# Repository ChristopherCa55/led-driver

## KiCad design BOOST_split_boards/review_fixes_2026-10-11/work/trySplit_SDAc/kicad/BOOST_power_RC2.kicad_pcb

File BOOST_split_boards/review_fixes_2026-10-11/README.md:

# Review fixes, 2026-10-11 (work folder)

Fixes for the 2026-10-10 schematic and PCB reviews, run from `review_2026-10-10/FIX_PROMPT.md`.

- **The copy:** `led-driver/BOOST_review_fixes/` = BOOST_package as of 2026-10-11 (12 key files hash-checked against
  all three shipped folders; lock files, `.history` and `.kicad_prl` left out), plus `NOT_FOR_FAB.txt`.
- **The shipped folders are never written.**
- **Status (2026-10-13):** every approved step is in the copy (steps 1-4, 5g, 6b, 7e, 8c, 9, 10) and every output
  was regenerated; the copy stays NOT_FOR_FAB until the user says ship. Read the top of `FIX_REPORT.md`, then
  `CHANGES_XY.md`.
- **Answers:** `ANSWERS.md` (the user's words and how each was applied).

## Layout
- `DECISIONS.md`: the decisions asked in one batch, with numbers, options and recommendations.
- `work/baseline/`: every check on the unmodified copy (run on a scratch copy of its KiCad folder, so no `.kicad_prl`
  lands in the copy).
- `work/METRICS.md`: one row per metric, one column per step; `work/METRICS_final.md`: baseline / the copy now / with
  the pending steps. `work/CHANGELOG.md`: every step, failed tries included. `work/promotions.log`: every file written
  into the copy, old -> new hash.
- `work/stepNN/`: each step's scratch KiCad folder, its spec, gates (`step_checks.log`), metrics outputs and `STEP.md`.
  Failed tries keep their folder with a `FAILED.txt` or `SUPERSEDED.txt`.
- `work/specs/`: the edit specs (pcb_text_edit / route_new / add_footprints jobs).
- `work/final_copy_check/`: the final gates run on the copy's own files.
- `work/pristine/`: untouched copies of the copy's KiCad and LTspice folders, the references for checks.
- `work/proto/*_NOT_FOR_FAB/`: research prototypes on scratch boards. These are not steps of the fix.
- `work/whatif/`: what-if solves on edited copies of the copper export.
- `work/sims/`: LTspice runs (`.save` list; the shipped `.tran`).
- `work/mockups/`, `img/mock/`: note and title mock-ups (scratch schematics only).
- `img/research/`: net maps used for planning.

## Tools (`tools/`)
| Tool | What it does |
|---|---|
| `make_copy.py` | Makes the copy, leaving out lock files and KiCad backups; checks every copied file's hash. |
| `step_checks.sh STEP` | Runs every gate and metric on `STEP/kicad`: ERC x3, DRC with refill and parity, sync, both exports, DC solve, loop L, pcb_checks, plane / sense cover, gate returns, GND heatmap with sense offsets, card sens_check6, and the U16 thermal model (`THERMAL=1`). |
| `collect.py WORK STEP...` | Builds METRICS.md and flags anything worse than the baseline. |
| `sense_cover.py` | Sense nets over GND. Rebuilt; reproduces the 10-02 per-net figures exactly. |
| `sense_offsets.py` | LED-sense GND offsets to the card's GND. Rebuilt; reproduces 10-02 exactly. |
| `gates_all.sh` | gate_return.py for all ten gate paths. |
| `sim_case.py` | One LTspice run on a scratch copy, editing the netlist only (`.save` list, extra `.meas`, `.ic` variants). |
| `d19_cycles.py` | D19 conduction per switching cycle from a run. |
| `pcb_text_edit.py SPEC IN OUT` | Removes / adds segments and vias by text edit (CRLF kept); OUT must not exist. |
| `whatif_vias.py` | Adds vias to a copper export, with antipads and a collision check. |
| `net_map.py` | Plan view of a net on all layers. |
| `mock_notes.py`, `mock_kicad.py` | Note and title mock-ups into new scratch files. |

## Lessons
- **Run heavy jobs one at a time.** Two 9-worker DC solves at once crash (BrokenProcessPool, out of memory). Running
  solves alongside LTspice grew the page file to 46 GB.
- **Headless Edge from Python** writes no screenshot when its output is piped. Log it to a file and wait for the PNG.
- **DC solves run out of memory with 5-9 workers** while the user's apps hold ~20 GB; 3 workers work (~30 min).
- **A via with no track or pad needs `(free yes)`**, or KiCad gives it a zone's net (step 7's first try became 5V).
- **The card's GND is in the Power netclass (0.25 mm clearance)**, not Default (0.2 mm).
- **Never edit a bash script while it runs** (bash reads it as it goes; step 3's make_step.sh broke that way).
- **Git Bash's `grep -c $'\r'` counts every line**: count CRLF in Python.
- **The 6-layer card is saturated:** the longest In1 splitters (0err_hi, SDA) have no route on In2 / F / B.

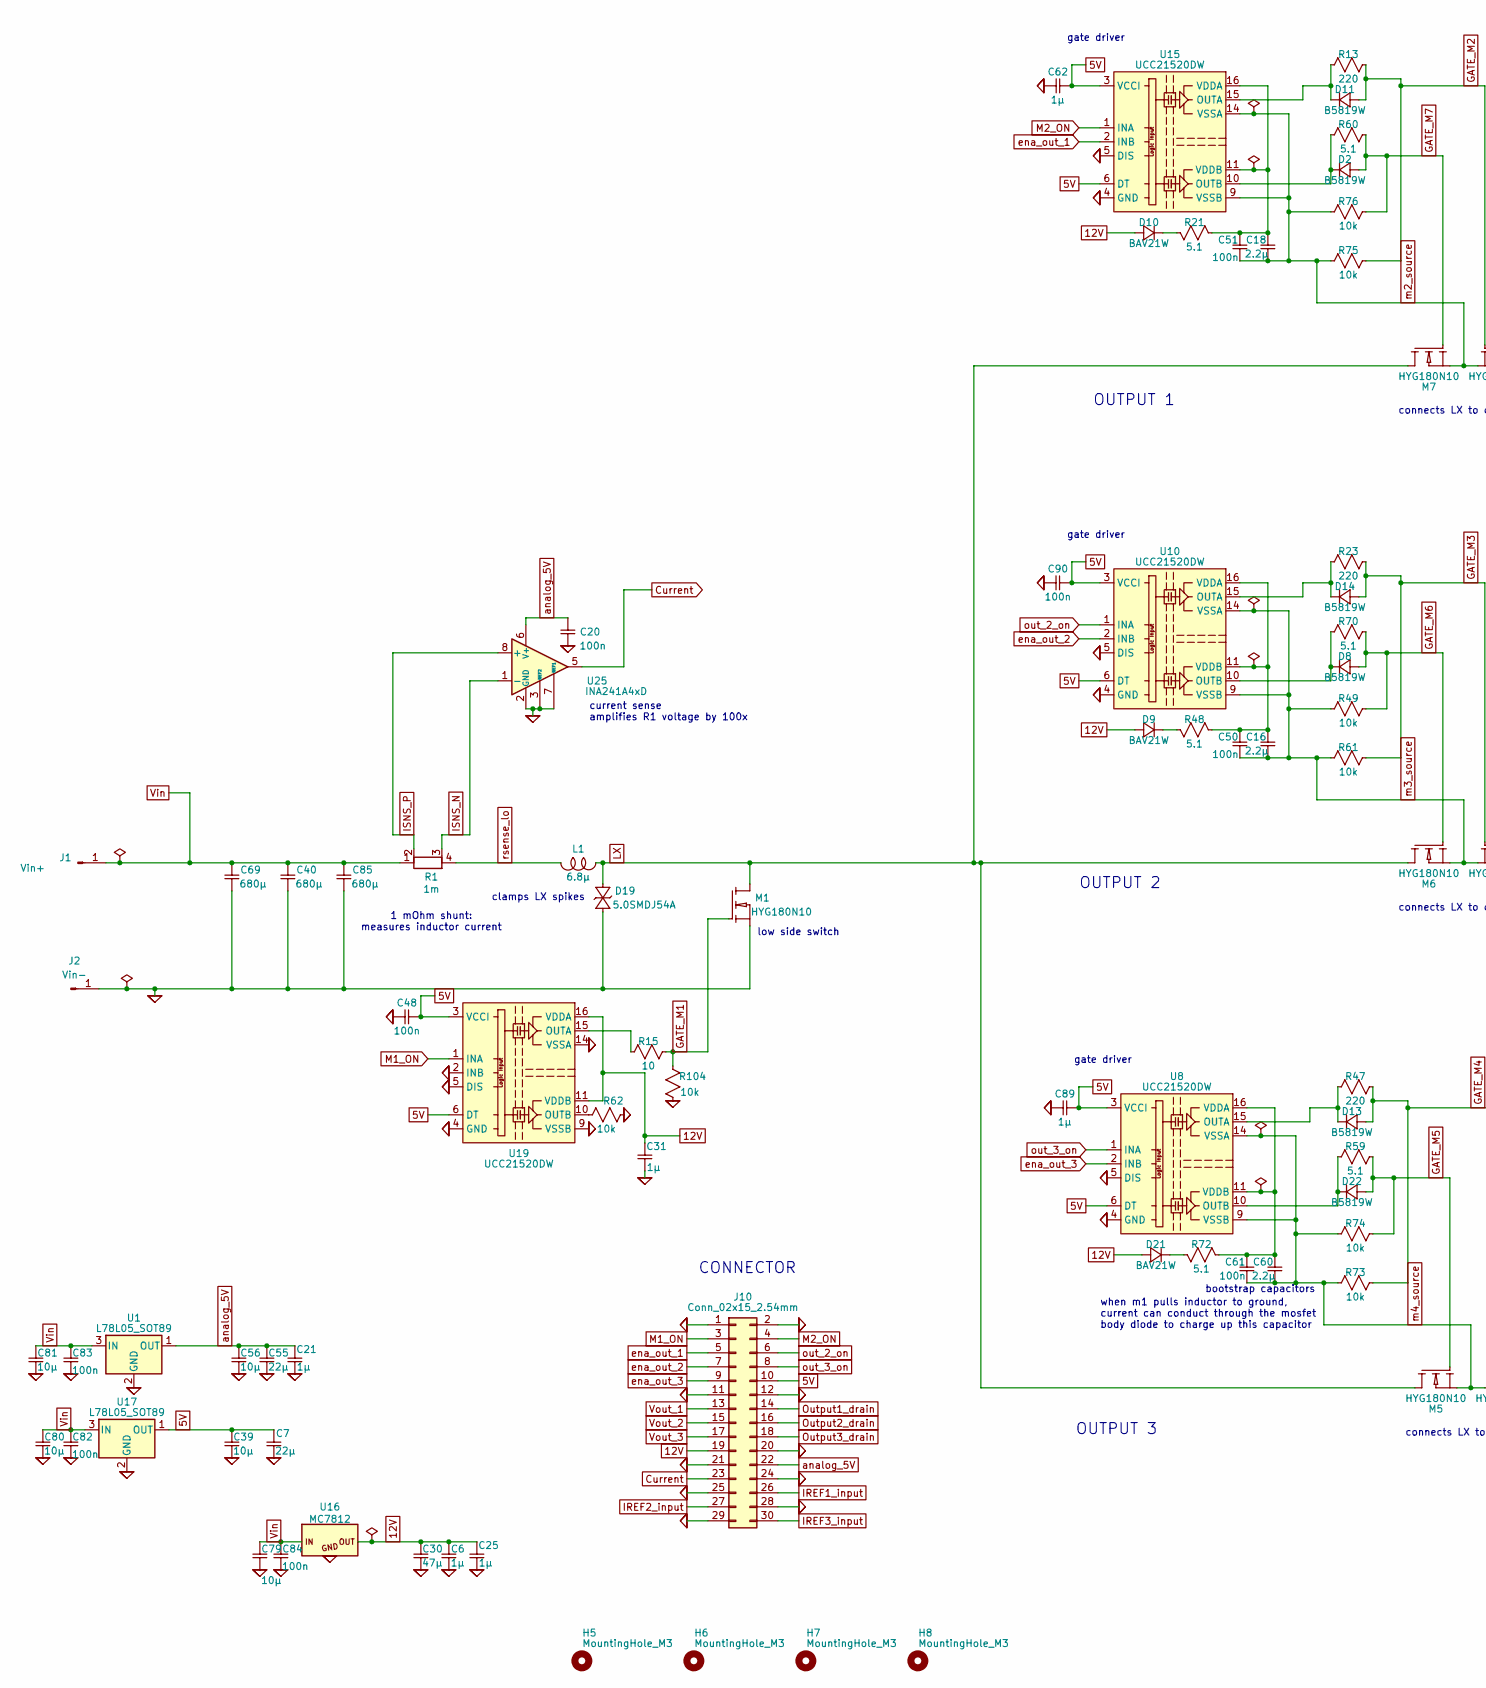
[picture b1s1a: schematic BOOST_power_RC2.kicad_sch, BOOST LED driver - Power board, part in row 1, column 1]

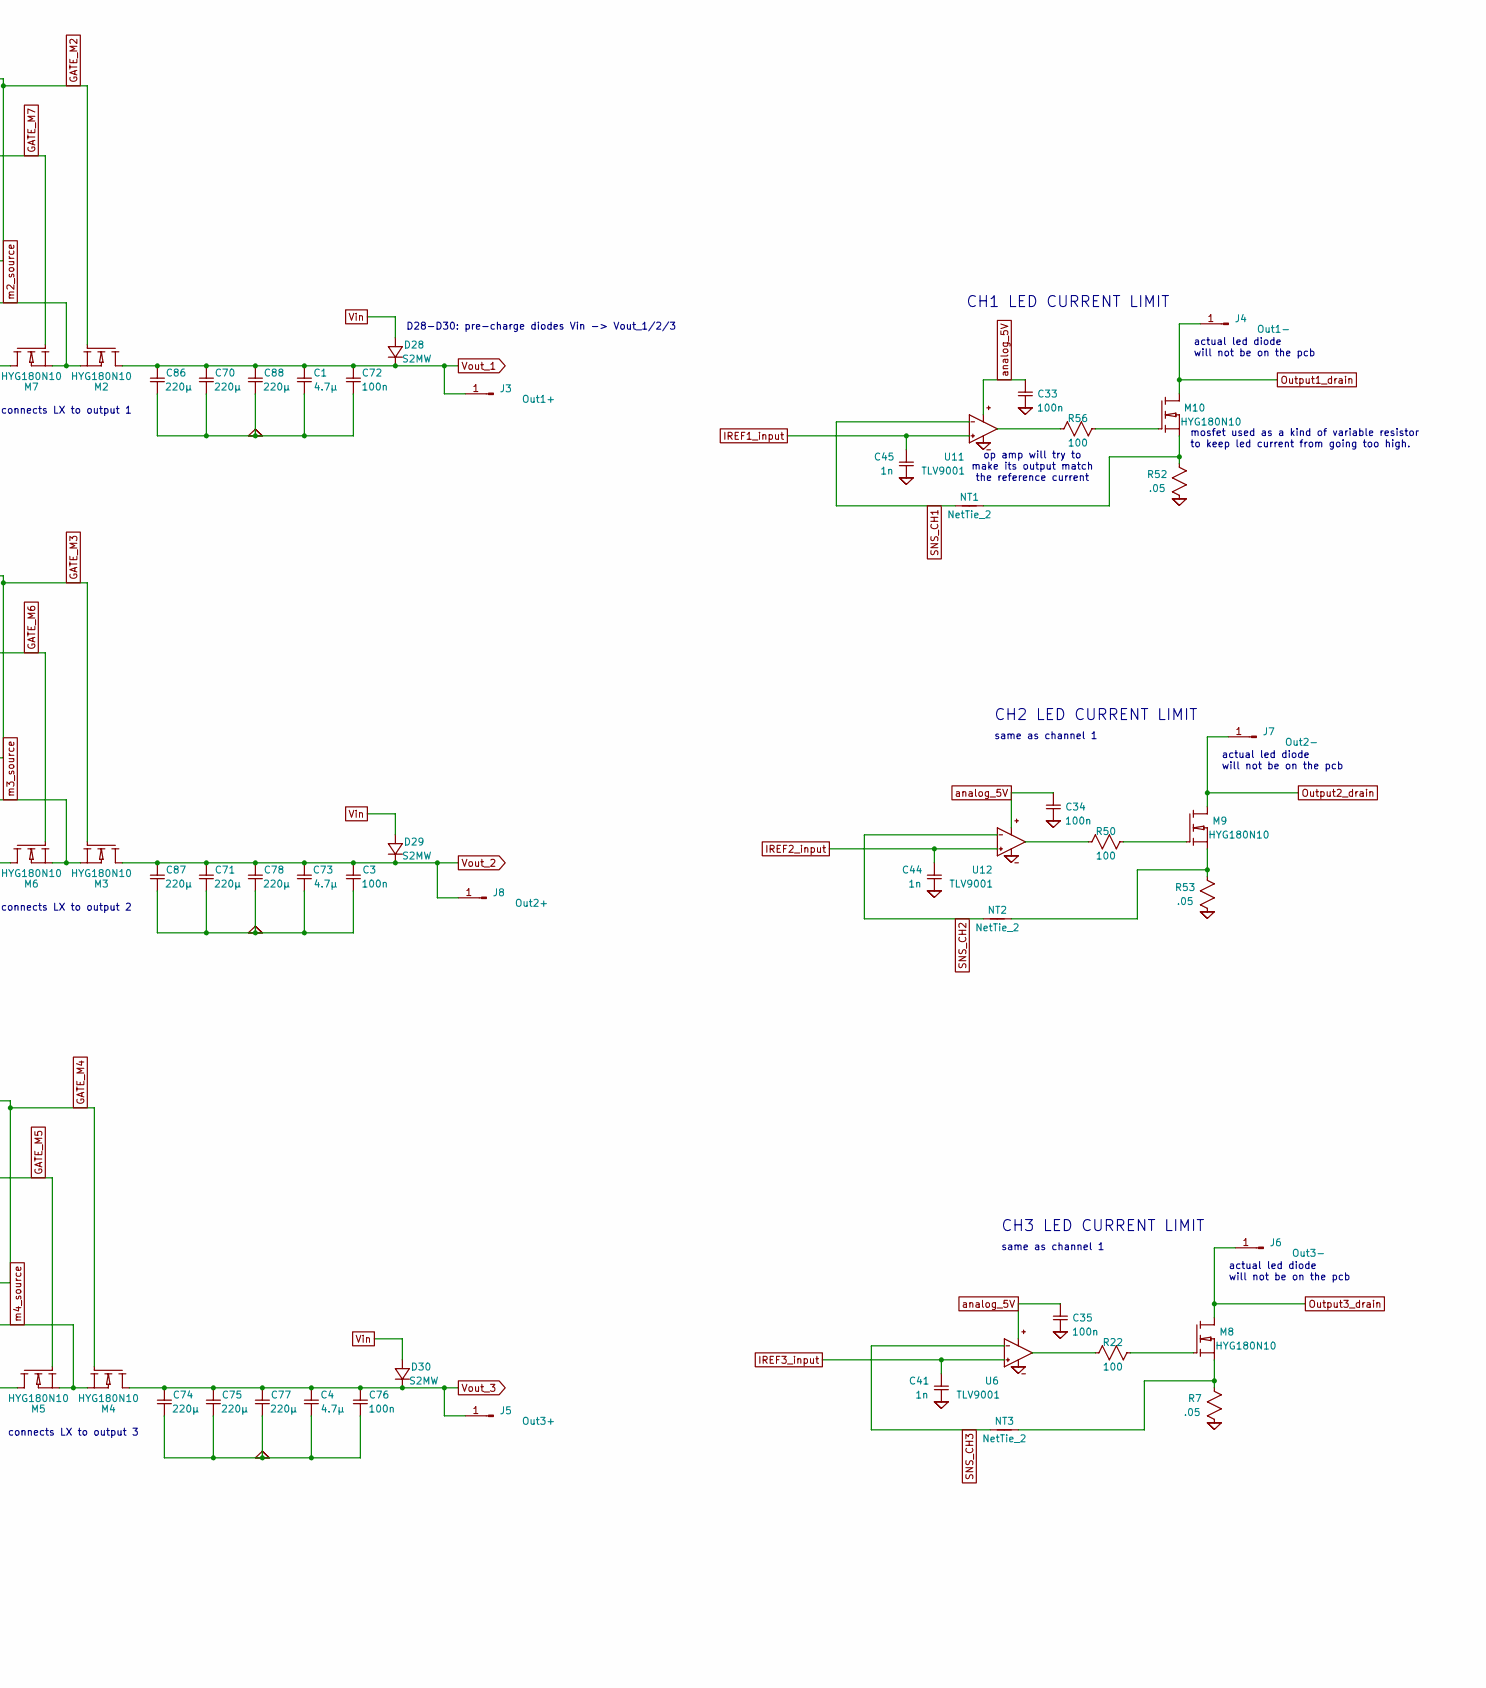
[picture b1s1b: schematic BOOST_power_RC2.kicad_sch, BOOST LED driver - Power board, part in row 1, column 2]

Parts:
C1, C4, C73: 4.7µ; C_1210_3225Metric
C3, C72, C76: 100n; C_0805_2012Metric
C6, C21, C25, C31, C62, C89: 1µ; C_0805_2012Metric
C7, C55: 22µ; C_1210_3225Metric; MPN GRM32ER71E226KE15L; LCSC C21397
C16, C18, C60: 2.2µ; C_1206_3216Metric
C20, C33, C34, C35, C48, C50, C51, C61, C82, C83, C84, C90: 100n; C_0603_1608Metric
C30: 47µ; CP_EIA-7343-31_Kemet-D; MPN TR3D476K025C0250; LCSC C4979367
C39, C56, C79, C80, C81: 10µ; C_1210_3225Metric
C40, C69, C85: 680µ; CP_Elec_10x12.5; MPN EEH-ZU1E681UP; LCSC C29664285
C41, C44, C45: 1n; C_0603_1608Metric
C70, C71, C75, C77, C78, C88: 220µ; CP_Elec_10x16.5; MPN EEH-ZS1H221P
C74, C86, C87: 220µ; CP_Elec_10x16.5; MPN EEH-ZU1H221P
D2, D8, D11, D13, D14, D22: B5819W; D_SOD-123
D9, D10, D21: BAV21W; D_SOD-123
D19: 5.0SMDJ54A; D_SMC; MPN 5.0SMDJ54A; LCSC C20415356
D28, D29, D30: S2MW; D_SOD-123F; MPN S2MW; LCSC C128729
H5, H6, H7, H8: MountingHole_M3; MountingHole_3.2mm_M3
J1: Vin+; MountingHole_4.3mm_M4_Pad7.0_TopBottom
J2: Vin-; MountingHole_4.3mm_M4_Pad7.0_TopBottom
J3: Out1+; TestPoint_THTPad_4.0x4.0mm_Drill2.0mm
J4: Out1-; TestPoint_THTPad_4.0x4.0mm_Drill2.0mm
J5: Out3+; TestPoint_THTPad_4.0x4.0mm_Drill2.0mm
J6: Out3-; TestPoint_THTPad_4.0x4.0mm_Drill2.0mm
J7: Out2-; TestPoint_THTPad_4.0x4.0mm_Drill2.0mm
J8: Out2+; TestPoint_THTPad_4.0x4.0mm_Drill2.0mm
J10: Conn_02x15_2.54mm; PinSocket_2x15_P2.54mm_Vertical; MPN ESQ-115-44-G-D
L1: 6.8µ; IND_CSCF3218-6R8MC
M1, M8, M9, M10: HYG180N10; TO-220-3_Horizontal_TabUp_M2.5
M2, M3, M4, M5, M6, M7: HYG180N10; TO-220-3_Horizontal_TabUp_NoHole
NT1, NT2, NT3: NetTie_2; NetTie-2_SMD_Pad0.5mm
R1: 1m; R_Bourns_CSS4J-4026; MPN CSS4J-4026R-1L00F; LCSC C2076400
R7, R52, R53: .05; R_2512_6332Metric
R13, R23, R47: 220; R_0603_1608Metric
R15: 10; R_0805_2012Metric
R21, R48, R60, R72: 5.1; R_0805_2012Metric; MPN 0805W8F510KT5E; LCSC C17724
R22, R50, R56: 100; R_0603_1608Metric
R49, R61, R62, R73, R74, R75, R76, R104: 10k; R_0603_1608Metric
R59, R70: 5.1; R_0805_2012Metric
U1, U17: L78L05_SOT89; SOT-89-3
U6, U11, U12: TLV9001; SOT-23-5; MPN TLV9001IDBVR
U8, U10, U15, U19: UCC21520DW; SOIC-16W_7.5x10.3mm_P1.27mm
U16: MC7812; TO-263-3_TabPin2; MPN MC7812BD2TR4G
U25: INA241A4xD; SOIC-8_3.9x4.9mm_P1.27mm; MPN INA241A4IDR; LCSC C22427873

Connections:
5V: C7.1, C39.1, C48.1, C62.2, C89.2, C90.1, J10.10, U8.3 (VCCI), U8.6 (DT), U8.8 (VCCI), U10.3 (VCCI), U10.6 (DT), U10.8 (VCCI), U15.3 (VCCI), U15.6 (DT), U15.8 (VCCI), U17.1 (OUT), U19.3 (VCCI), U19.6 (DT), U19.8 (VCCI)
12V: C6.1, C25.1, C30.1, C31.1, D9.2 (+), D10.2 (+), D21.2 (+), J10.19, U16.3 (OUT), U19.11 (VDDB), U19.16 (VDDA)
Current: J10.23, U25.5
GATE_M1: M1.1 (G), R15.2, R104.1
GATE_M2: D11.2 (+), M2.1 (G), R13.1, R75.2
GATE_M3: D14.2 (+), M3.1 (G), R23.2, R61.2
GATE_M4: D13.2 (+), M4.1 (G), R47.1, R73.2
GATE_M5: D22.2 (+), M5.1 (G), R59.1, R74.2
GATE_M6: D8.2 (+), M6.1 (G), R49.1, R70.2
GATE_M7: D2.2 (+), M7.1 (G), R60.2, R76.2
GND: C1.2, C3.2, C4.2, C6.2, C7.2, C20.2, C21.2, C25.2, C30.2, C31.2, C33.2, C34.2, C35.2, C39.2, C40.2, C41.2, C44.2, C45.2, C48.2, C55.2, C56.2, C62.1, C69.2, C70.2, C71.2, C72.2, C73.2, C74.2, C75.2, C76.2, C77.2, C78.2, C79.2, C80.2, C81.2, C82.2, C83.2, C84.2, C85.2, C86.2, C87.2, C88.2, C89.1, C90.2, D19.2 (+), J2.1, J10.1, J10.2, J10.11, J10.12, J10.20, J10.21, J10.24, J10.25, J10.28, J10.29, M1.3 (S), R7.2, R52.2, R53.2, R62.2, R104.2, U1.2 (GND), U6.2 (V-), U8.4 (GND), U8.5 (DIS), U10.4 (GND), U10.5 (DIS), U11.2 (V-), U12.2 (V-), U15.4 (GND), U15.5 (DIS), U16.2 (GND), U17.2 (GND), U19.2 (INB), U19.4 (GND), U19.5 (DIS), U19.9 (VSSB), U19.14 (VSSA), U25.2 (GND), U25.3 (REF2), U25.4 (GND), U25.7 (REF1)
IREF1_input: C45.1, J10.26, U11.3 (In+)
IREF2_input: C44.1, J10.27, U12.3 (In+)
IREF3_input: C41.1, J10.30, U6.3 (In+)
ISNS_N: R1.3, U25.1 (-)
ISNS_P: R1.2, U25.8 (+)
LX: D19.1 (-), L1.1, M1.2 (D), M5.2 (D), M6.2 (D), M7.2 (D)
M1_ON: J10.3, U19.1 (INA)
M2_ON: J10.4, U15.1 (INA)
unnamed: D2.1 (-), R60.1, U15.10 (OUTB)
unnamed: D8.1 (-), R70.1, U10.10 (OUTB)
unnamed: D9.1 (-), R48.1
unnamed: D10.1 (-), R21.1
unnamed: D11.1 (-), R13.2, U15.15 (OUTA)
unnamed: D13.1 (-), R47.2, U8.15 (OUTA)
unnamed: D14.1 (-), R23.1, U10.15 (OUTA)
unnamed: D21.1 (-), R72.1
unnamed: D22.1 (-), R59.2, U8.10 (OUTB)
unnamed: M8.1 (G), R22.1
unnamed: M8.3 (S), NT3.2, R7.1
unnamed: M9.1 (G), R50.1
unnamed: M9.3 (S), NT2.2, R53.1
unnamed: M10.1 (G), R56.1
unnamed: M10.3 (S), NT1.2, R52.1
unnamed: R22.2, U6.1 (OUT)
unnamed: C60.1, C61.1, R72.2, U8.11 (VDDB), U8.16 (VDDA)
unnamed: C16.1, C50.1, R48.2, U10.11 (VDDB), U10.16 (VDDA)
unnamed: R56.2, U11.1 (OUT)
unnamed: R50.2, U12.1 (OUT)
unnamed: C18.1, C51.1, R21.2, U15.11 (VDDB), U15.16 (VDDA)
unnamed: R15.1, U19.15 (OUTA)
unnamed: R62.1, U19.10 (OUTB)
Output1_drain: J4.1 (Pin_1_1), J10.14, M10.2 (D)
Output2_drain: J7.1 (Pin_1_1), J10.16, M9.2 (D)
Output3_drain: J6.1 (Pin_1_1), J10.18, M8.2 (D)
SNS_CH1: NT1.1, U11.4 (In-)
SNS_CH2: NT2.1, U12.4 (In-)
SNS_CH3: NT3.1, U6.4 (In-)
Vin: C40.1, C69.1, C79.1, C80.1, C81.1, C82.1, C83.1, C84.1, C85.1, D28.2 (+), D29.2 (+), D30.2 (+), J1.1, R1.1, U1.3 (IN), U16.1 (IN), U17.3 (IN)
Vout_1: C1.1, C70.1, C72.1, C86.1, C88.1, D28.1 (-), J3.1 (Pin_1_1), J10.13, M2.2 (D)
Vout_2: C3.1, C71.1, C73.1, C78.1, C87.1, D29.1 (-), J8.1 (Pin_1_1), J10.15, M3.2 (D)
Vout_3: C4.1, C74.1, C75.1, C76.1, C77.1, D30.1 (-), J5.1 (Pin_1_1), J10.17, M4.2 (D)
analog_5V: C20.1, C21.1, C33.1, C34.1, C35.1, C55.1, C56.1, J10.22, U1.1 (OUT), U6.5 (V+), U11.5 (V+), U12.5 (V+), U25.6 (V+)
ena_out_1: J10.5, U15.2 (INB)
ena_out_2: J10.7, U10.2 (INB)
ena_out_3: J10.9, U8.2 (INB)
m2_source: C18.2, C51.2, M2.3 (S), M7.3 (S), R75.1, R76.1, U15.9 (VSSB), U15.14 (VSSA)
m3_source: C16.2, C50.2, M3.3 (S), M6.3 (S), R49.2, R61.1, U10.9 (VSSB), U10.14 (VSSA)
m4_source: C60.2, C61.2, M4.3 (S), M5.3 (S), R73.1, R74.1, U8.9 (VSSB), U8.14 (VSSA)
out_2_on: J10.6, U10.1 (INA)
out_3_on: J10.8, U8.1 (INA)
rsense_lo: L1.2, R1.4

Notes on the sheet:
CH1 LED CURRENT LIMIT
OUTPUT 1
OUTPUT 2
current sense amplifies R1 voltage by 100x
gate driver
CH2 LED CURRENT LIMIT
when m1 pulls inductor to ground, current can conduct through the mosfet body diode to charge up this capacitor
OUTPUT 3
same as channel 1
op amp will try to make its output match the reference current
low side switch
mosfet used as a kind of variable resistor to keep led current from going too high.
1 mOhm shunt: measures inductor current
bootstrap capacitors
connects LX to output 3
clamps LX spikes
CH3 LED CURRENT LIMIT
CONNECTOR
D28-D30: pre-charge diodes Vin -> Vout_1/2/3
connects LX to output 2
actual led diode will not be on the pcb
connects LX to output 1

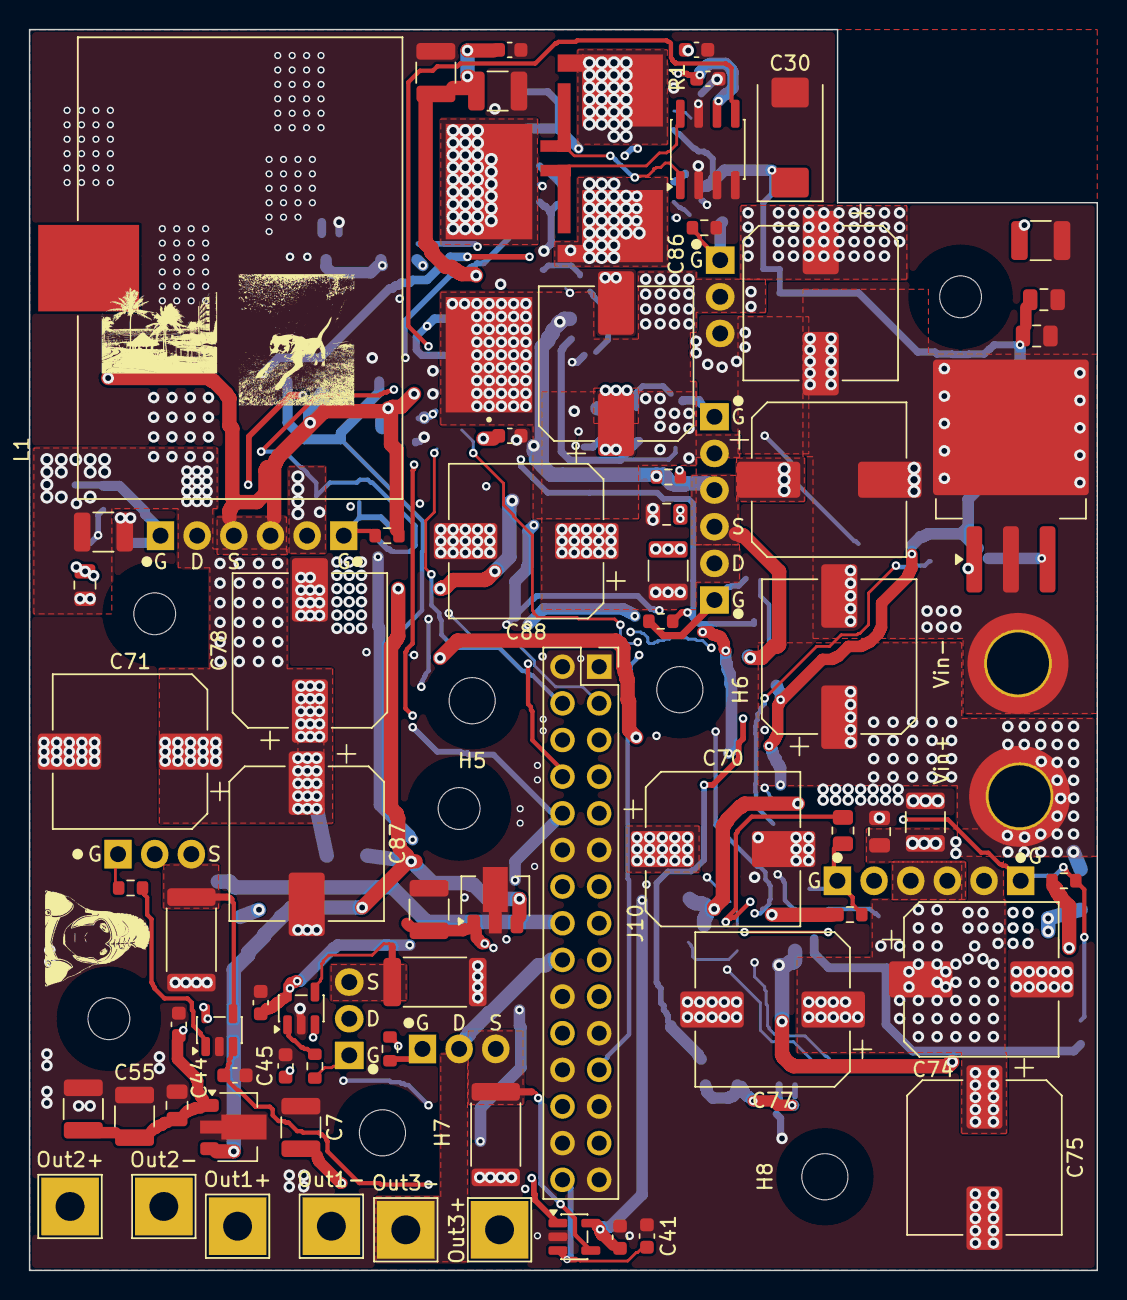
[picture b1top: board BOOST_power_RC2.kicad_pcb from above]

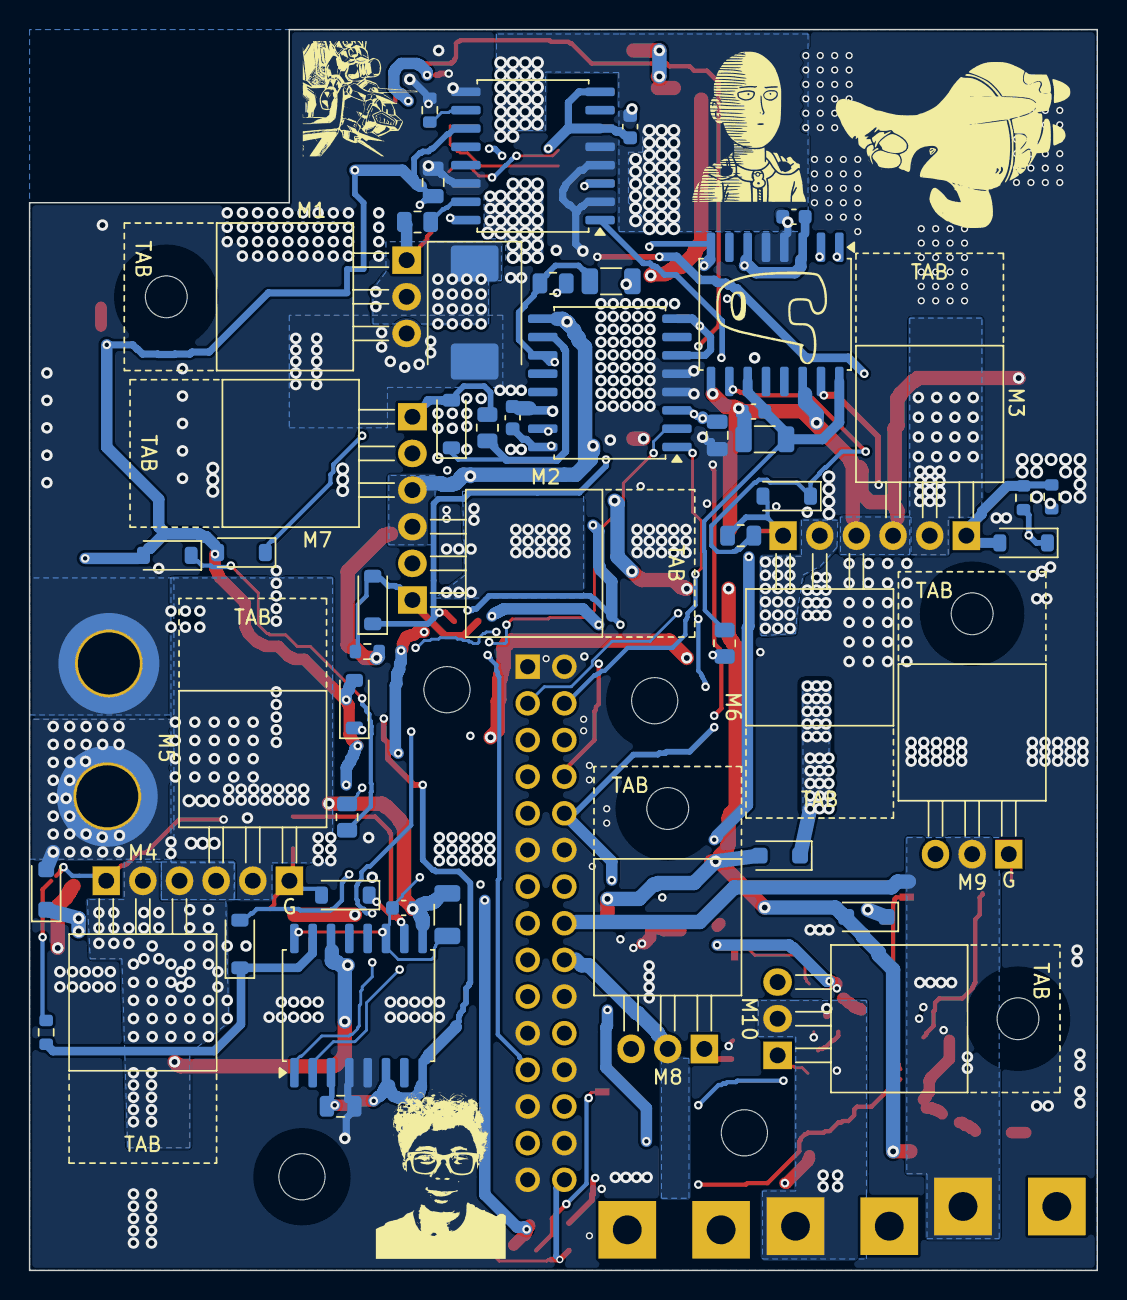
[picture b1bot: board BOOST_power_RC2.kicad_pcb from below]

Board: 6 copper layers, 74.0 x 86.0 mm, 126 parts (49 on the bottom side), 62 nets.
